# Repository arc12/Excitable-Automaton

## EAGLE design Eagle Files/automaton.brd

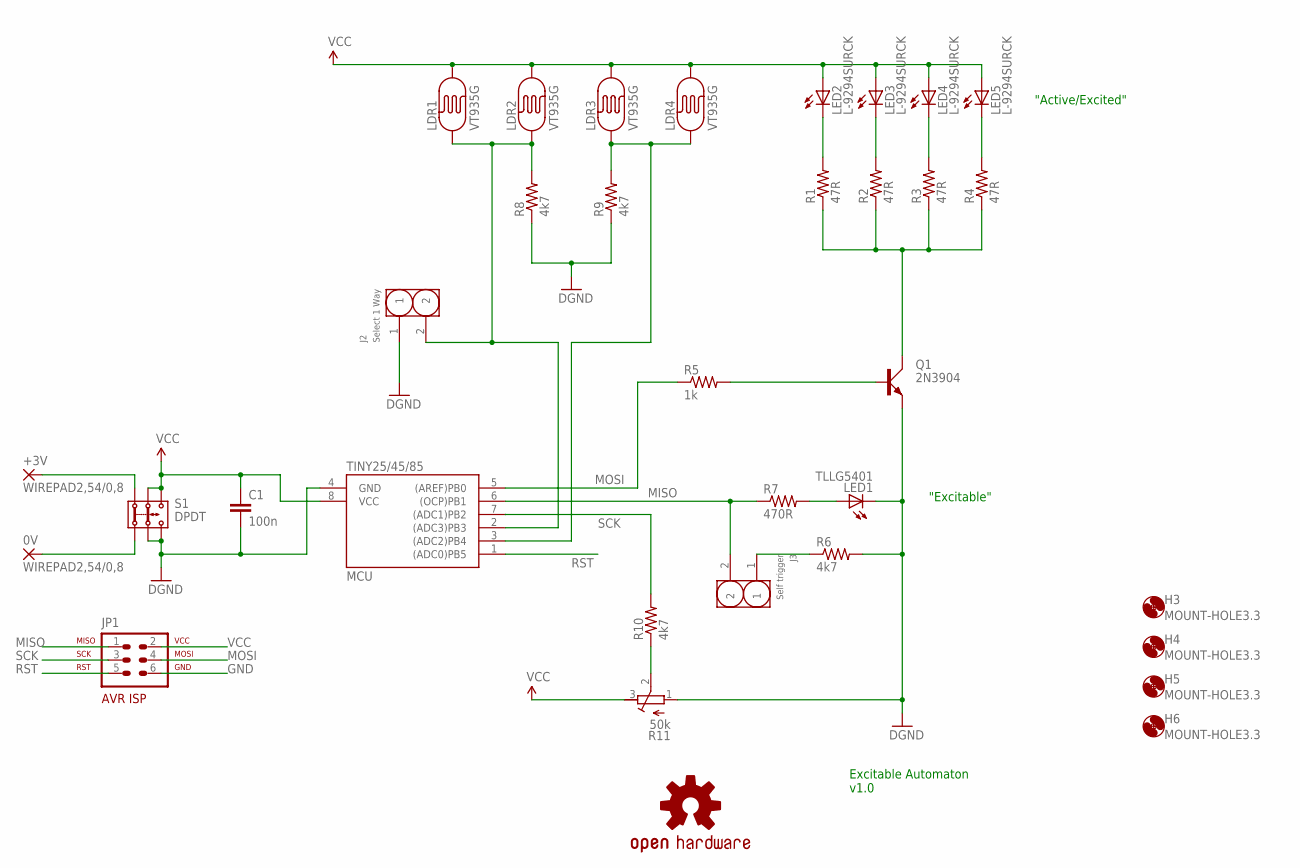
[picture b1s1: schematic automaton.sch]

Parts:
0V: WIREPAD2,54/0,8; 2,54/0,8
+3V: WIREPAD2,54/0,8; 2,54/0,8
C1: 100n; C10B4
H3, H4, H5, H6: MOUNT-HOLE3.3; 3,3
J2: Select 1 Way; 2P-2.54
J3: Self trigger; 2P-2.54
JP1: AVR-ISP-6VERT; AVR-ISP-6
LDR1, LDR2, LDR3, LDR4: VT935G; PHOTOCELL
LED1: TLLG5401; LED5MM
LED2, LED3, LED4, LED5: L-9294SURCK; LED5MM
LOGO1: OSHW-LOGOS; OSHW-LOGO-S
MCU: TINY25/45/85; DIL08
Q1: 2N3904; TO92D
R1, R2, R3, R4: 47R; AXIAL-0.3
R5: 1k; AXIAL-0.3
R6, R8, R9, R10: 4k7; AXIAL-0.3
R7: 470R; AXIAL-0.3
R11: 50k; RTRIM3296Y
S1: DPDT; 2P2T

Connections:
GND: C1.2, J2.1, JP1.6, LED1.K (C), MCU.4 (GND), Q1.E, R6.P$2 (2), R8.P$1 (1), R9.P$1 (1), R11.1 (E), S1.2.2, S1.3.2
MISO: J3.2, JP1.1, MCU.6 ((OCP)PB1), R7.P$1 (1)
MOSI: JP1.4, MCU.5 ((AREF)PB0), R5.P$1 (1)
unnamed: J2.2, LDR1.1, LDR2.1, MCU.2 ((ADC3)PB3), R8.P$2 (2)
unnamed: LED5.K (C), R4.P$2 (2)
unnamed: LED2.K (C), R1.P$2 (2)
unnamed: LED3.K (C), R2.P$2 (2)
unnamed: LED4.K (C), R3.P$2 (2)
unnamed: Q1.C, R1.P$1 (1), R2.P$1 (1), R3.P$1 (1), R4.P$1 (1)
unnamed: Q1.B, R5.P$2 (2)
unnamed: 0V.1, S1.1.2
unnamed: +3V.1, S1.1.1
unnamed: J3.1, R6.P$1 (1)
unnamed: R10.P$1 (1), R11.2 (S)
unnamed: LED1.A, R7.P$2 (2)
unnamed: LDR3.1, LDR4.1, MCU.3 ((ADC2)PB4), R9.P$2 (2)
RST: JP1.5, MCU.1 ((ADC0)PB5)
SCK: JP1.3, MCU.7 ((ADC1)PB2), R10.P$2 (2)
VCC: C1.1, JP1.2, LDR1.2, LDR2.2, LDR3.2, LDR4.2, LED2.A, LED3.A, LED4.A, LED5.A, MCU.8 (VCC), R11.3 (A), S1.2.1, S1.3.1

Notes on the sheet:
"Excitable"
"Active/Excited"
Excitable Automaton v1.0

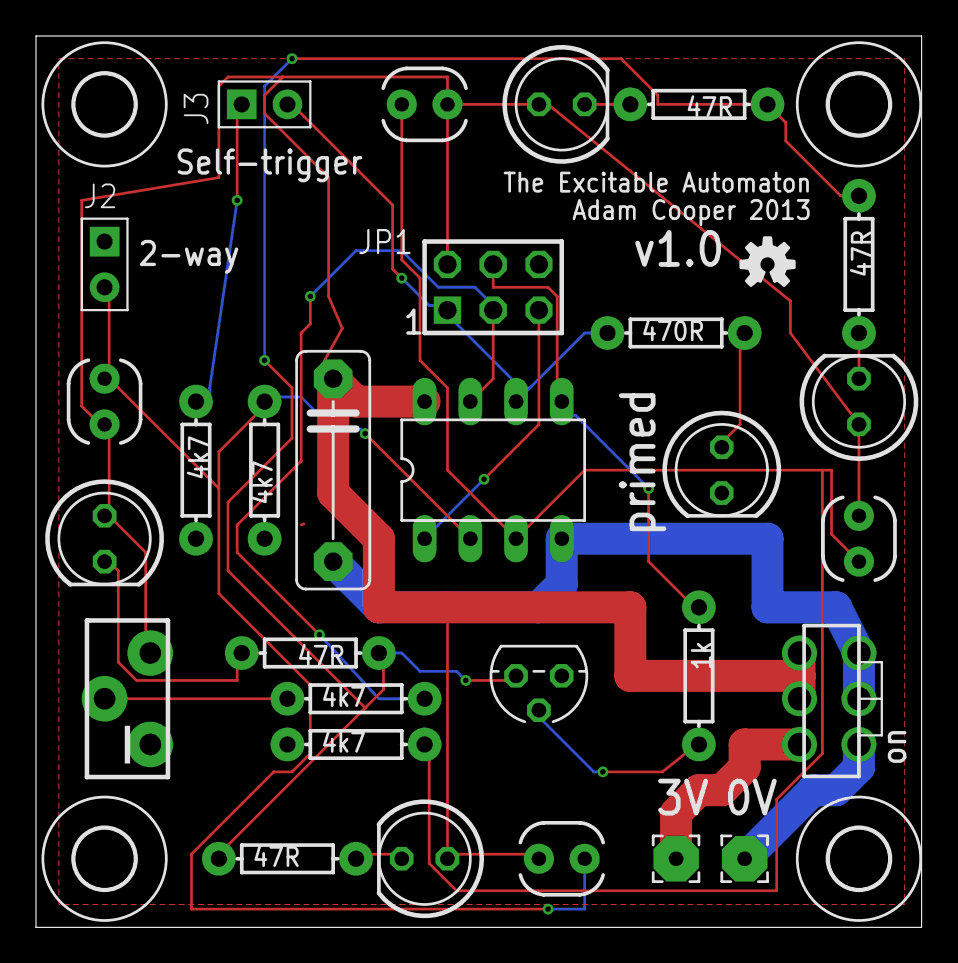
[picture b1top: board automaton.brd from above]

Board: 2 copper layers, 49.2 x 49.5 mm, 34 parts (0 on the bottom side), 19 nets.

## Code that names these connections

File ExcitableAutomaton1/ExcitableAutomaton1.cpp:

/*
 * ExcitableAutomaton1.cpp
 *
 * Created: 02/12/2012 17:08:48
 *  Author: Adam
 */ 

/* ========================
        Design Notes
   ========================
A. Device
---------
ATtiny85V - this is the low voltage version so that 2xAA cells can be used to power it

B. Fuses
--------
SELFPRGEN = [ ]
RSTDISBL = [ ]
DWEN = [ ]
SPIEN = [X]
WDTON = [ ]
EESAVE = [ ]
BODLEVEL = DISABLED
CKDIV8 = [ ]
CKOUT = [ ]
SUT_CKSEL = WDOSC_128KHZ_6CK_14CK_4MS

C. Operating Conditions
-----------------------
Main clock: 32kHz (128kHz int clock prescaled by 4). This gives an ADC clock that is outside datasheet recs but it seems OK
Timer1 clock: 7.8125Hz (main clock prescaled by 4096).

D. Jumpers
----------
jumperST = jumper pin to enable self-triggering
Pullup used- LOW input value enables behaviour. Jumper read on reset

*/

#include <avr/io.h>
#include <avr/interrupt.h>
#include <avr/sleep.h>
#include <avr/wdt.h>

#define nop() asm volatile("nop") 

//stereotypes
int readADC(char mux);

/* ====================
*    I/O Assignments
*  ====================*/
//ADCs use alternative assignments of Port B
const char ldr1Mux = 3;//PB3 = ADC3 : LDR input to ADCs. The order doesn't matter.
const char ldr2Mux = 2;//PB4 = ADC2
const char potMux = 1;//PB2 = ADC1 : potentiometer for trigger threshold setting. ADC connection
const char ADCD = 0x1C;//this is a mask for the ADCxD in DIDR. It must match the choice of ADC pins above

//Port B 0-2 for digital IO
const char led = PB0;//LEDS for "Excited" signalling
const char led_dir = (1<<DDB0);
const char jumperST = PB1;//jumper to enable self-triggering
const char jumperST_dir = (1<<DDB1);

/* ====================
*  Operating parameters
*  ====================*/
// time periods for the watchdog timer. The values are WDP2, WDP1 and WDP0
//		0 = 16ms
//		1 = 32ms
//		2 = 64ms
//		3 = 0.125s
//		4 = 0.25s
//		5 = 0.5s
//		6 = 1s
//		7 = 2s
//		higher values will probably stop things working!
const char t_refractory = 6;//refractory period
const char t_delay = 4;//delay between trigger event (light pulse detected) and excitation
const char t_excited = 3;//duration of the excitation (output LEDs on)

// time period for timer 1. Max value=0xFF See Design Notes above for timer clock period 
const char t_self =32;//this is the self-triggering delay count (from the end of the refractory period). 

//Jumper flags
bool selfTrigger = false;

int main(void)
{
	/* ==================
	*    Initialisation
	*  ==================*/

	//set PORTB to input with pullup enabled to read in jumper settings. low input means enable behaviour
	DDRB = 0x00;//all inputs
	PORTB = (1<<jumperST);//pullup
			
	//read in the jumper settings.
	nop();//see data sheet - "sync latch" means we need a clock cycle delay
	selfTrigger =!(0x01 & (PINB>>jumperST));
	
	//now turn the jumper pins into outputs (jumperST is used to output to a low power "I'm excitable" LED)
	PORTB = 0x00;//datasheet says we should tristate as an intermediate to changing direction with output 0
	DDRB |= jumperST_dir;
	
	//setup ADC input; this is not the default port/pin config
	ADMUX = potMux | (1<<ADLAR); // MUX set to threshold pot. VCC as ref. Left justified
	ADCSRA = (1<<ADEN); // turn ADC on and initialise. no auto-trigger, no interrupt. prescaler to div2
	DIDR0 = ADCD; //disable digital circuitry on the pins used for analog input
	
	//change data direction for LED output
	DDRB |= led_dir;
		
	//set the clock pre-scaler to give 32kHz clock
	CLKPR = 0x80;//change enable
	CLKPR = (1<<CLKPS1); //div by 4
		
	//power-down sleep is used several times with different watchdog timer periods.
	//set the sleep mode to power-down and enable sleep
	MCUCR |= (1<<SE)|(1<<SM1);
		
	// timer1 will be used for self-triggering using normal (non-PWM) mode and t_self as the output compare	
	if(selfTrigger){
		// set the prescaler to 4096 (see design notes section) and the mode.
		TCCR1 = (1<<CS13) | (1<<CS12) | (1<<CS10);//this also ensures "Normal port operation, OC0A/OC0B disconnected"
		//set the compare value to t_self
		OCR1A = t_self;
	}else{
		TCCR1 = 0x00;//disable timer
	}		
		
	//set up the watchdog timer
	//reset the counter
	__asm__ __volatile__ ("wdr");
	//enable the timer, configure for interrupt rather than reset, set to 2s
	WDTCR = (1<<WDIE) | 0x7; //but not WDE!!!!!!!!!!!!!!!!!! If WDE then reset on timeout will occur after the first interrupt - read the datasheet carefully!!!!!
	//enable interrupts at global level. The watchdog uses interrupts to wake up from power-down sleep.
	sei();
	
	/* ==================
	*      Operation
	*  ==================*/
    while(1)
    {
		//>>>>>>>>>>> Automaton is REFRACTORY <<<<<<<<<<<<<
		//LEDs must be off
		PORTB &= ~(1<<led);
		
		//set watchdog timer
		__asm__ __volatile__ ("wdr");//reset the timer
		WDTCR &= 0xF8;//clear existing prescaler period
		WDTCR |= t_refractory;// set WDP2, WDP1 and WDP0 with the timeout period
		//go into sleep mode until WDT timeout
		__asm__ __volatile__ ("sleep\n\t"::);
		
		
		//>>>>>>>>>>> Automaton is now EXCITABLE  <<<<<<<<<<<<< (or about to be...)
		//disable the watchdog timer interrupt (probably not strictly necessary since the interrupt handler would just return)
		WDTCR &=~(1<<WDIE);
			
		// prepare for self-triggering
		TCNT1 = 0;//reset the counter
		TIFR |= (1<<OCF1A);//reset the compare flag
		
		//signal "I am excitable" to a small output LED
		PORTB |= (1<<jumperST);

		//loop awaiting a trigger (external or self)
		bool adcNeutral = true;//becomes false if ADCs detect above-threshold change on an LDR channel
		int potVal=0;
		int ldr1Val=0x3FF;//max ADC value
		int ldr2Val=0x3FF;
		int ldr1Last=0;
		int ldr2Last=0;
		while(adcNeutral){
			//read in the trigger threshold. NB this is the required delta between readings
			//This is done inside the loop so that adjustments become active without requiring a trigger.
			potVal = readADC(potMux)/8;
			//store previous readings
			ldr1Last = ldr1Val;
			ldr2Last = ldr2Val;
			//read ADCs attached to LDRs
			ldr1Val = readADC(ldr1Mux);
			ldr2Val = readADC(ldr2Mux);
			//check for trigger conditions
			//ldr1 triggered		
			if(ldr1Val-potVal >= ldr1Last){
				adcNeutral = false;				
			}
			//ldr2 triggered
			if(ldr2Val-potVal >= ldr2Last){
				adcNeutral = false;
			}
			//force a trigger condition if compare flag for timer 1 is set 
			if(TIFR & (1<<OCF1A)){
				adcNeutral = false;
			}
		}
		//cancel "I am excitable" signal
		PORTB &= ~(1<<jumperST);
				
		//>>>>>>>>>>> Automaton is ACTIVATING  <<<<<<<<<<<<< (delay between trigger and EXCITED)
		__asm__ __volatile__ ("wdr");//reset the timer
		WDTCR &= 0xF8;//clear existing prescaler period
		WDTCR |= (1<<WDIE) | t_delay;// set the timeout period (and re-enable int)
		//go into sleep mode until WDT timeout
		__asm__ __volatile__ ("sleep\n\t"::);
		

		//>>>>>>>>>>> Automaton is EXCITED  <<<<<<<<<<<<<
		//LEDS go on
		PORTB |= (1<<led);
		
		//stay excited for t_excited
		__asm__ __volatile__ ("wdr");//reset the timer
		WDTCR &= 0xF8;//clear existing prescaler period
		WDTCR |= t_excited;//re-enable the watchdog timer and set WDP2, WDP1 and WDP0 with the timeout period
		//go into sleep mode until WDT timeout
		__asm__ __volatile__ ("sleep\n\t"::);		
    }
}

//read a 10bit precision value from the ADC specified by mux (see ADMUX). This is blocking single-shot.
int readADC(char mux){
	//assert the mux, VCC as ref. Left justified
	ADMUX = mux ;
	//start a conversion
	ADCSRA |= (1<<ADSC);
	//wait for end of conversion
	while (ADCSRA & (1<<ADSC));
	//compose the result. 
	int resL = ADCL; //read low first
	int resH = (int)ADCH<<8; //NB the cast to int before shifting
	int result = resH | resL;
	return result;
}

/*
*The watchdog timeout interrupt handler
*/	
ISR(WDT_vect)
{
	//doesn't actually do anything but the interrupt will have brought the MCU out of sleep
}

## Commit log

2013-01-01 eagle files temp commit

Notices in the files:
parts and their libraries:
SparkFun-Resistors: Licensing: CC v3.0 Share-Alike You are welcome to use this library for commercial purposes.
